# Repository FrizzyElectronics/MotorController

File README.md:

# MotorController
This board is a two motors controller. It uses two L9110 to drive the two DC motors individually making it the perfect module to control a robot. Its reduced footprint makes it easy to integrate in any design.

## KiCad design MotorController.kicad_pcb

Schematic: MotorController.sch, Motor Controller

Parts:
C1: 10uF; C_0805_HandSoldering
C2, C3, C4: 0.1uF; C_0805_HandSoldering
D1: LED; LED_0805
P1: MOTOR_2; JST_PH_S2B-PH-K_02x2.00mm_Angled
P2: CONN_01X06; Pin_Header_Straight_1x06_Pitch2.54mm
P!1: MOTOR_1; JST_PH_S2B-PH-K_02x2.00mm_Angled
R1: 1K; R_0805_HandSoldering
R2, R3, R4, R5: 10K; R_0805_HandSoldering
U1, U2: L9110; SOIC-8-N

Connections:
GND: C1.2, C2.2, D1.1 (K), P2.4, U1.5 (GND), U1.8 (GND), U2.5 (GND), U2.8 (GND)
unnamed: C3.1, P!1.2, U1.1 (OA)
unnamed: C3.2, P!1.1, U1.4 (OB)
unnamed: C4.1, P1.2, U2.1 (OA)
unnamed: C4.2, P1.1, U2.4 (OB)
unnamed: D1.2 (A), R1.2
unnamed: P2.1, R2.2, U1.7 (IB)
unnamed: P2.2, R3.2, U1.6 (IA)
unnamed: P2.5, R4.2, U2.7 (IB)
unnamed: P2.6, R5.2, U2.6 (IA)
VCC: C1.1, C2.1, P2.3, R1.1, R2.1, R3.1, R4.1, R5.1, U1.2 (VCC), U1.3 (VCC), U2.2 (VCC), U2.3 (VCC)

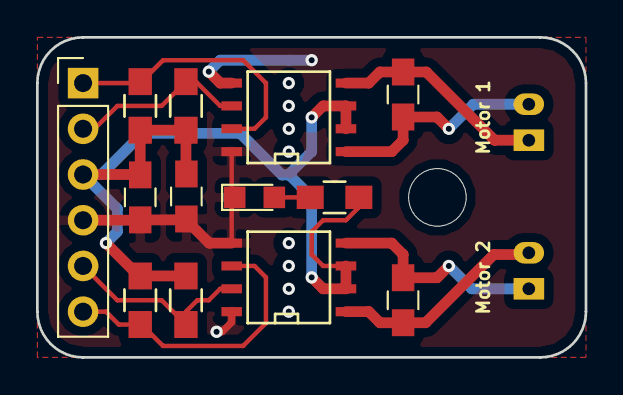
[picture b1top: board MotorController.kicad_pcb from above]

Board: 2 copper layers, 30.5 x 17.8 mm, 15 parts (0 on the bottom side), 11 nets.

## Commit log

2017-04-10 Add license file
2017-04-10 ERC Passed
2017-04-10 Finished Schematic Files
2017-04-10 Layout terminado sin serigrafia
2017-04-10 Layout terminado con serigrafia
2017-04-14 valores, referencias y serigrafias de los dos conectores que se salen de la placa, escondidas
2017-04-14 Añadida serigrafia de pines, logo de MC y mandada a fabrica
2017-04-17 Test
    Test
2017-04-30 Guías de montaje / Assembly Guides
    Añadidas las guías de montaje / Assembly guides added
2017-04-30 Corregidos errores / Fixed errors
2018-01-20 Gerbers exportados
    Gerbers exportados para pruebas de panelizacion
2018-01-20 Gerbers exportados
    Gerbers exportados para prueba de panelizacion, carpeta de prueba antigua "gerbers" borrada
2018-02-12 Logo cambiado
2018-02-24 logo girado
2018-03-04 arbol de carpetas cambiado
2018-03-11 Updated module description
2018-05-06 BOM exportado
2018-05-06 gerbers generados
2018-06-10 datasheet subido
2018-07-14 Re-rellenado el plano de masa
2018-07-15 Gerbers exportados
